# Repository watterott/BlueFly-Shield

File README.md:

# BlueFly-Shield
The BlueFly-Shield is a plug-on module with WiFi/WLAN for Arduino based on a Microchip WINC1500 WiFi Network Controller SoC.

* Compatible with [Arduino WiFi-Shield-101](https://www.arduino.cc/en/Main/ArduinoWiFiShield101)
* [Microchip ATWINC1500B](http://www.microchip.com/wwwproducts/en/ATWINC1500) WiFi Network Controller (SPI)
* [Microchip ATECC508A](http://www.microchip.com/wwwproducts/en/ATECC508A) Crypto Authentication (I2C address 0x60)
* Integrated WiFi and IPv4 stack
* 3.3V - 5V tolerant IOs
* Open-Source and released under the [Creative Commons Attribution Share-Alike License](https://creativecommons.org/licenses/by-sa/4.0/).
* **[Documentation on learn.watterott.com](https://learn.watterott.com)**

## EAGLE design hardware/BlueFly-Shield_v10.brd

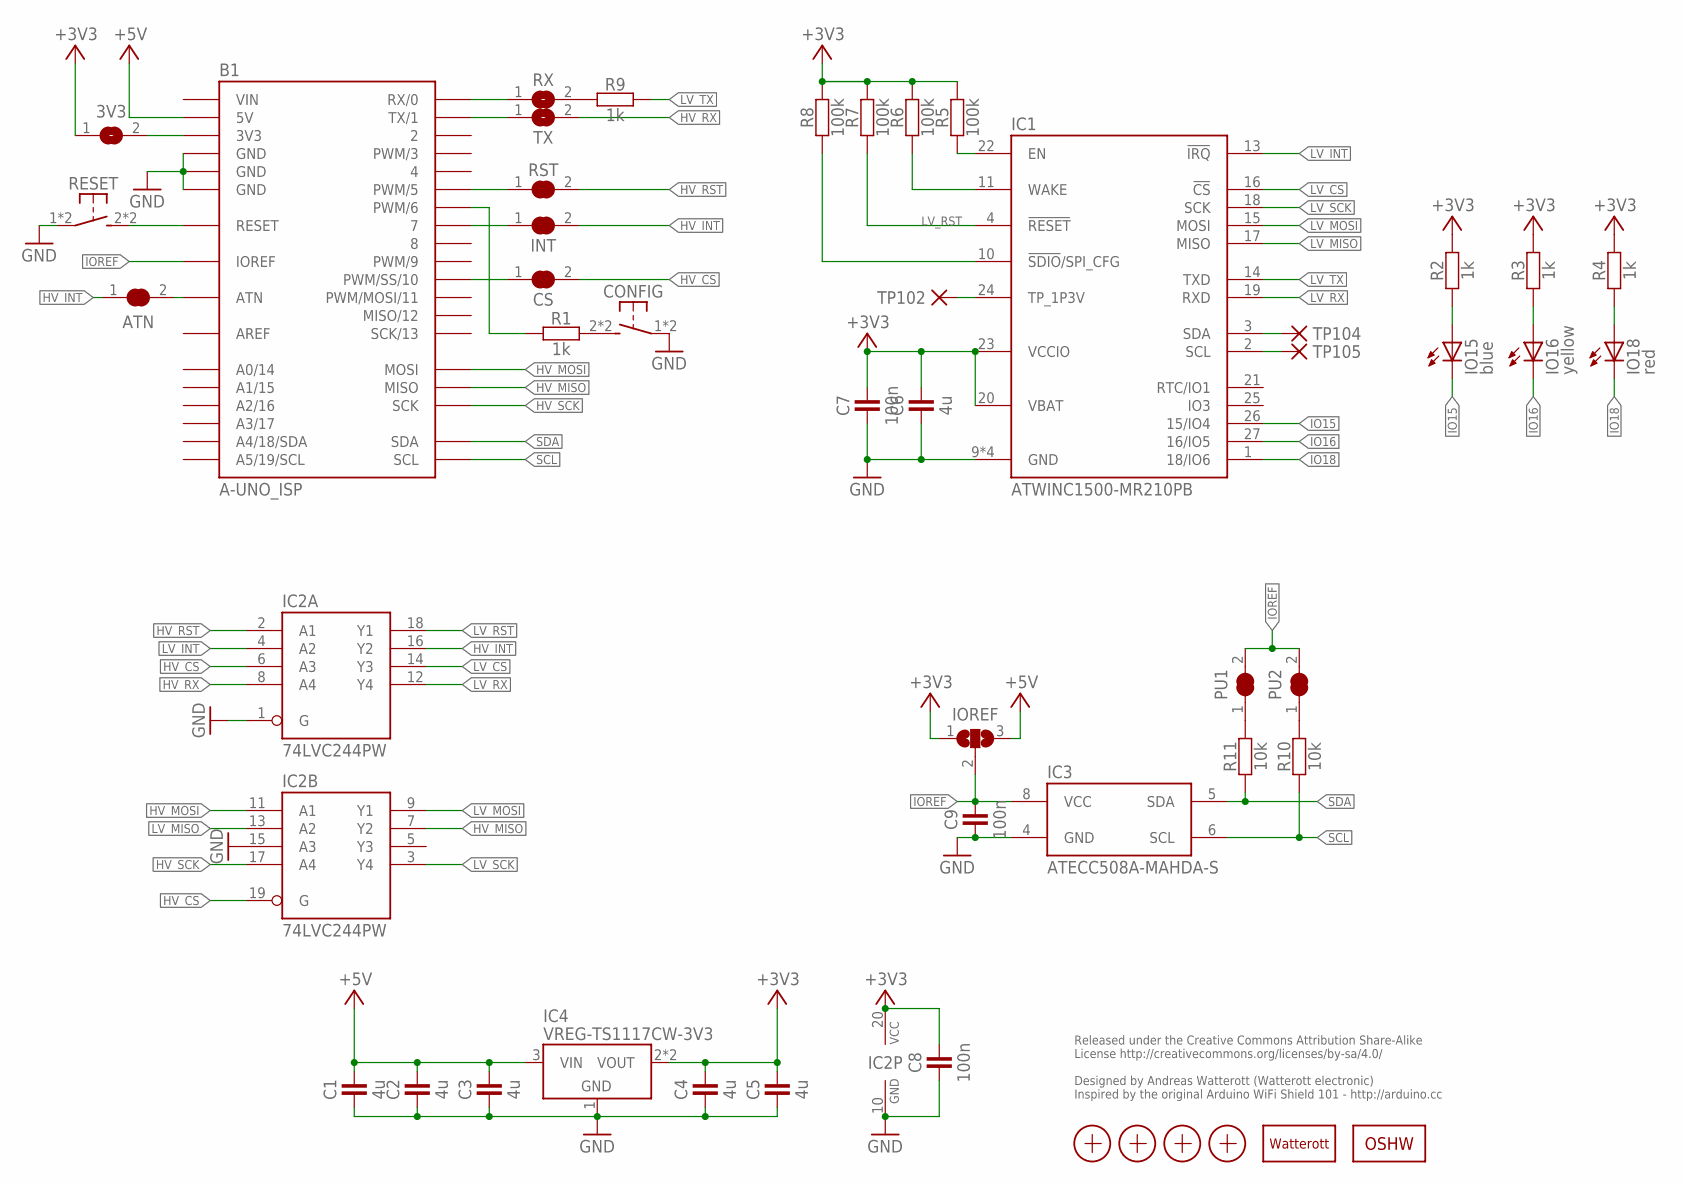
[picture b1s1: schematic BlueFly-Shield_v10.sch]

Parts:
3V3: JUMPER2-0603-NC; JUMPER2-0603_NC
ATN: JUMPER2-0603-NC; JUMPER2-0603_NC
B1: A-UNO_ISP; A-UNO-ISP
C1, C2, C3, C4, C5, C6: 4u; C0603
C7: 100n; C0603
C8, C9: 100n; C0402
CONFIG: SW-TACTILE-TL3315; TL3315N
CS: JUMPER2-0603-NC; JUMPER2-0603_NC
IC1: ATWINC1500-MR210PB; ATWINC1500-MX210
IC2: 74LVC244PW; TSSOP20
IC3: ATECC508A-MAHDA-S; UDFN8
IC4: VREG-TS1117CW-3V3; SOT223
INT: JUMPER2-0603-NC; JUMPER2-0603_NC
IO15: blue; C0603
IO16: yellow; C0603
IO18: red; C0603
IOREF: JUMPER3-0603-NC; JUMPER3-0603_NC
LOGO1: LOGO-S_PLACE_M; SPARK_TPLACE_M
LOGO2: OSHW_LOGOX0100; OSHW_6X100
PU1, PU2: JUMPER2-0603-NC; JUMPER2-0603_NC
R1, R2, R3, R4, R9: 1k; C0402
R5, R6, R7, R8: 100k; C0402
R10, R11: 10k; C0402
RESET: SW-TACTILE-TL3315; TL3315N
RST: JUMPER2-0603-NC; JUMPER2-0603_NC
RX: JUMPER2-0603-NC; JUMPER2-0603_NC
TP102, TP104, TP105: PAD-1.27X1.27_NC
TX: JUMPER2-0603-NC; JUMPER2-0603_NC
X1, X2, X3, X4: PASSER-07; PASSER_07MM

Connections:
3V3: 3V3.2, B1.3V3
+3V3: 3V3.1, C4.2, C5.2, C6.2, C7.2, C8.2, IC1.20 (VBAT), IC1.23 (VCCIO), IC2.20 (VCC), IC4.2 (VOUT), IC4.4 (VOUT), IOREF.1, R2.2, R3.2, R4.2, R5.2, R6.2, R7.2, R8.2
+5V: B1.5V, C1.2, C2.2, C3.2, IC4.3 (VIN), IOREF.3
AREF: B1.AREF
ATN: ATN.2, B1.ATN
BTN: CONFIG.2 (S1), CONFIG.3 (S1), R1.2
D0: B1.0 (RX/0), RX.1
D1: B1.1 (TX/1), TX.1
D5: B1.5 (PWM/5), RST.1
D7: B1.7, INT.1
D10: B1.10 (PWM/SS/10), CS.1
DF6: B1.6 (PWM/6), R1.1
GND: B1.GND@1 (GND), B1.GND@2 (GND), B1.GND@3 (GND), C1.1, C2.1, C3.1, C4.1, C5.1, C6.1, C7.1, C8.1, C9.1, CONFIG.1, CONFIG.4 (P1), IC1.9 (GND), IC1.12 (GND), IC1.28 (GND), IC1.GND, IC2.1 (G), IC2.10 (GND), IC2.15 (A3), IC3.4 (GND), IC4.1 (GND), RESET.1, RESET.4 (P1)
HV_CS: CS.2, IC2.6 (A3), IC2.19 (G)
HV_INT: ATN.1, IC2.16 (Y2), INT.2
HV_MISO: B1.MISO, IC2.7 (Y2)
HV_MOSI: B1.MOSI, IC2.11 (A1)
HV_RST: IC2.2 (A1), RST.2
HV_RX: IC2.8 (A4), TX.2
HV_SCK: B1.SCK, IC2.17 (A4)
IO15: IC1.26 (15/IO4), IO15.C
IO16: IC1.27 (16/IO5), IO16.C
IO18: IC1.1 (18/IO6), IO18.C
IOREF: B1.IOREF, C9.2, IC3.8 (VCC), IOREF.2, PU1.2, PU2.2
LED15: IO15.A, R2.1
LED16: IO16.A, R3.1
LED18: IO18.A, R4.1
LV_CS: IC1.16 (!CS), IC2.14 (Y3)
LV_EN: IC1.22 (EN), R5.1
LV_INT: IC1.13 (!IRQ), IC2.4 (A2)
LV_MISO: IC1.17 (MISO), IC2.13 (A2)
LV_MOSI: IC1.15 (MOSI), IC2.9 (Y1)
LV_RST: IC1.4 (!RESET), IC2.18 (Y1), R7.1
LV_RX: IC1.19 (RXD), IC2.12 (Y4)
LV_SCK: IC1.18 (SCK), IC2.3 (Y4)
LV_TX: IC1.14 (TXD), R9.2
LV_WAKE: IC1.11 (WAKE), R6.1
unnamed: R9.1, RX.2
unnamed: PU2.1, R10.2
unnamed: PU1.1, R11.2
RST: B1.RST@1 (RESET), RESET.2 (S1), RESET.3 (S1)
SCL: B1.SCL, IC3.6 (SCL), R10.1
SDA: B1.SDA, IC3.5 (SDA), R11.1
SPI_CFG: IC1.10 (!SDIO!/SPI_CFG), R8.1
TP: IC1.24 (TP_1P3V), TP102.1
VIN: B1.VIN
WIFI_SCL: IC1.2 (SCL), TP105.1
WIFI_SDA: IC1.3 (SDA), TP104.1

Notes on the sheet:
Released under the Creative Commons Attribution Share-Alike License http://creativecommons.org/licenses/by-sa/4.0/ Designed by Andreas Watterott (Watterott electronic) Inspired by the original Arduino WiFi Shield 101 - http://arduino.cc

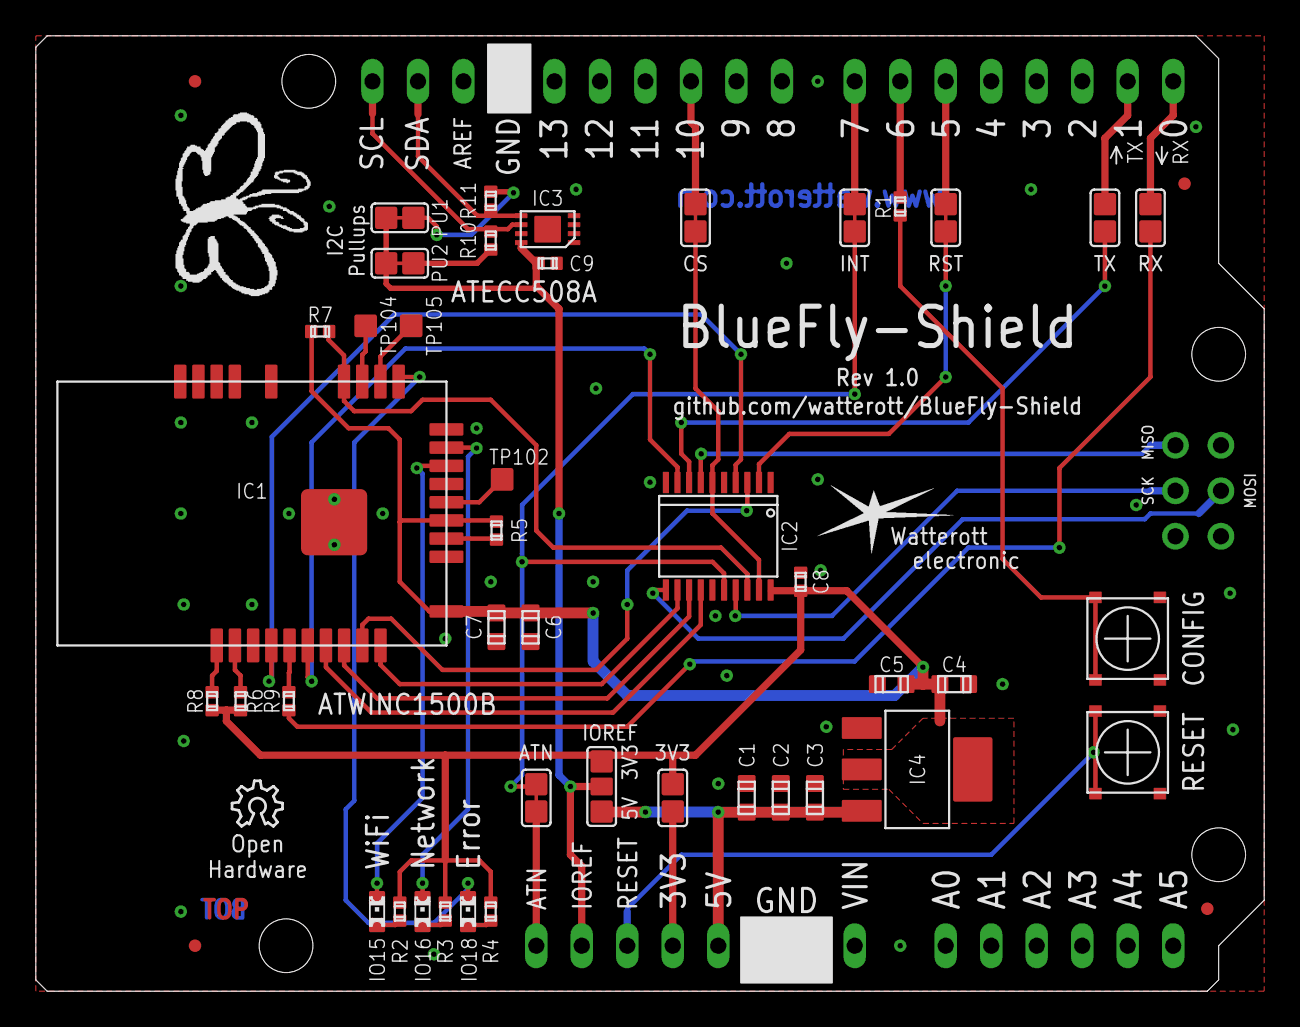
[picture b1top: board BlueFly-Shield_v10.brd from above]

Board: 2 copper layers, 68.6 x 53.3 mm, 49 parts (0 on the bottom side), 46 nets.
